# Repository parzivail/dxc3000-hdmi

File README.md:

# Sony DXC-3000A HDMI Conversion

This repository is split into multiple KiCad projects.

## MS9282 breakout

Contains the MS9282 breakout

Directory: `ms9282_carrier`

## DXC-3000A module template

Contains the blank PCB that matches the physical dimensions and 50-pin header of the backplane modules

Directory: `module_template`

## DXC-3000A module breakout

A few assets in this image:

The DXC-3000A backplane-to-FPC breakout board
* Directory: `module_breakout`

The video conditioner "shield" for the MS9282 breakout
* Directory: `ms9282_carrier_adapter`

Pairs with the MS9282 breakout from above.

## MS9282 module

Contains the complete MS9282-based EN-39 substitute for HDMI conversion. The image shows it in comparison with the original EN-39 module.

Directory: `ms9282_module`

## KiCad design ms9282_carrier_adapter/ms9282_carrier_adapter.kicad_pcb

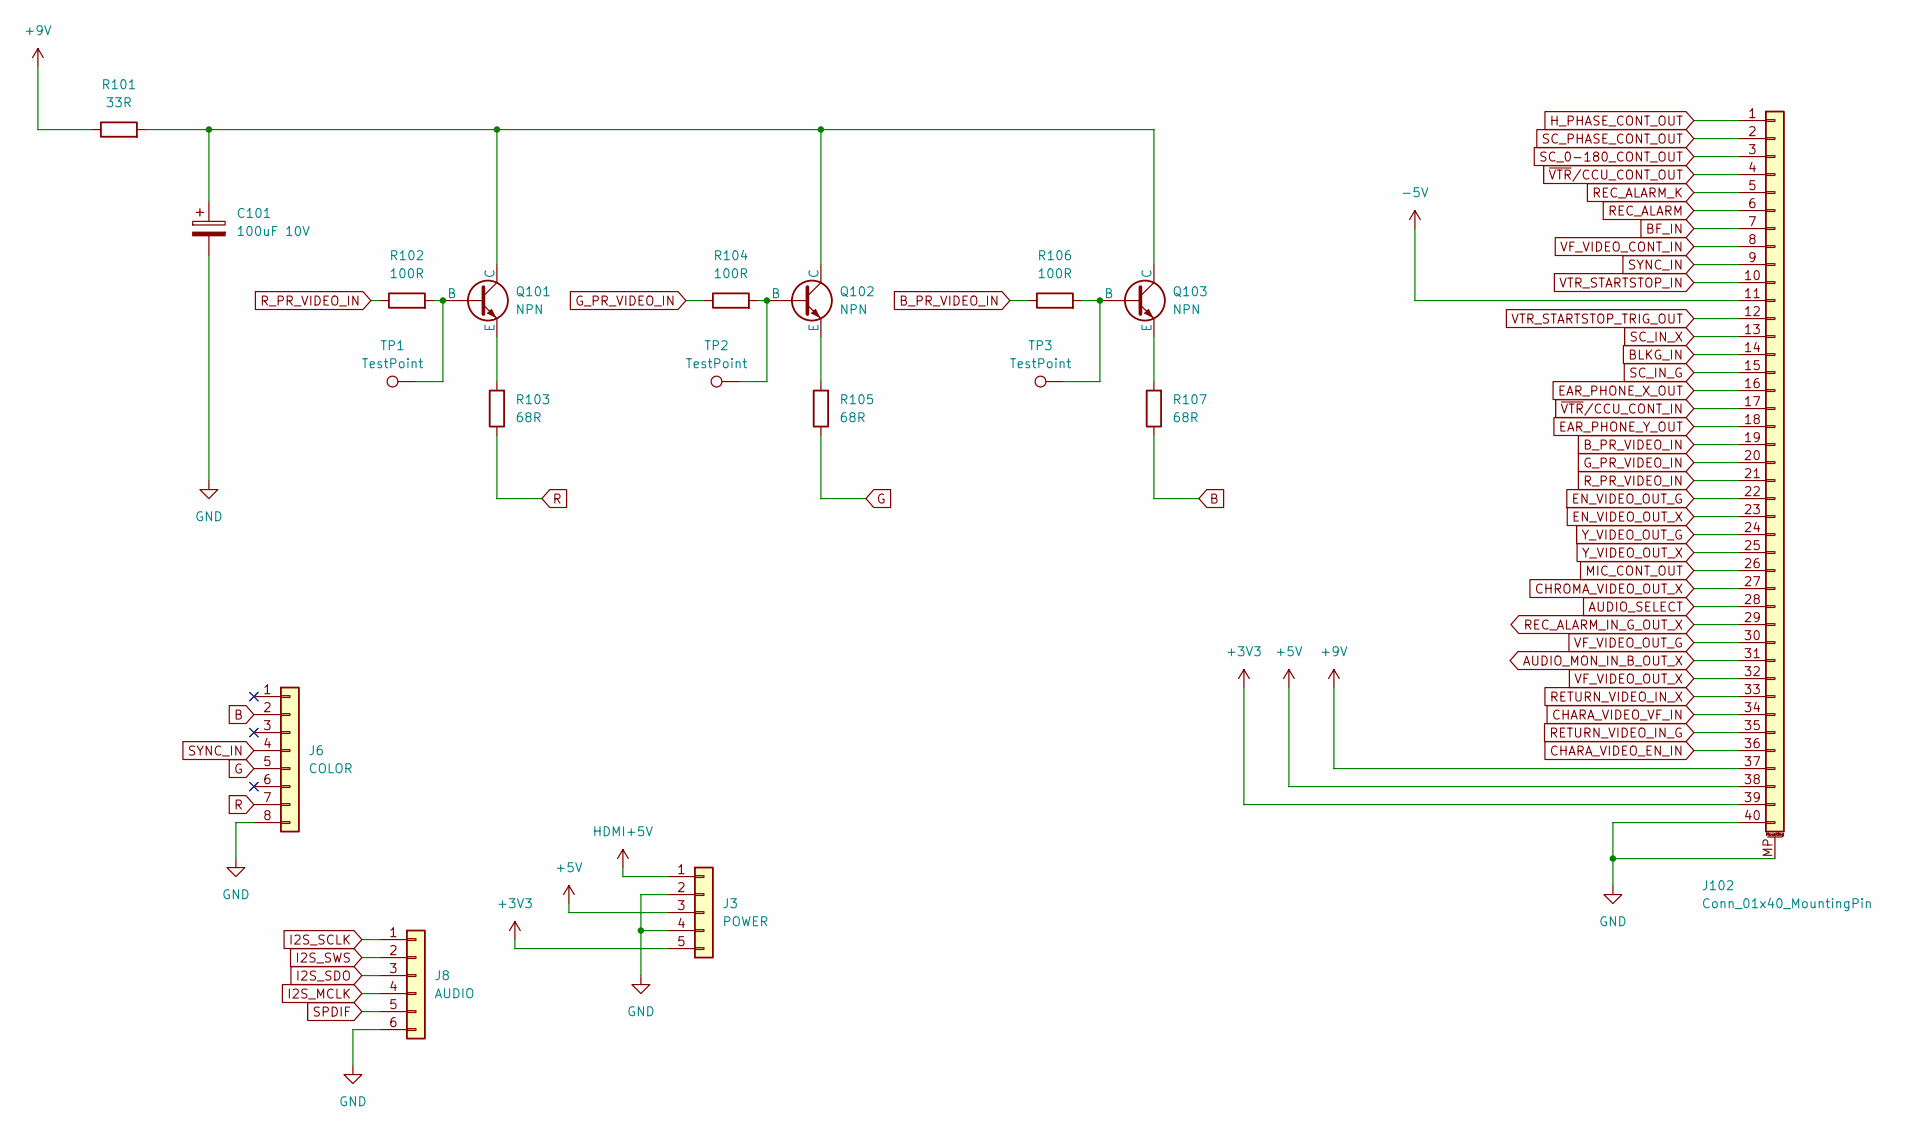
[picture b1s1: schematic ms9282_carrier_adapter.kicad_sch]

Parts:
C101: 100uF 10V; C_1206_3216Metric; LCSC Part C15008
J3: POWER; PinHeader_1x05_P2.54mm_Vertical
J6: COLOR; PinHeader_1x08_P2.54mm_Vertical
J8: AUDIO; PinHeader_1x06_P2.54mm_Vertical
J102: Conn_01x40_MountingPin; Hirose_FH12-40S-0.5SH_1x40-1MP_P0.50mm_Horizontal; LCSC Part C596725
Q101, Q102, Q103: NPN; SOT-23; LCSC Part C27829
R101: 33R; R_0402_1005Metric; LCSC Part C25105
R102, R104, R106: 100R; R_0402_1005Metric; LCSC Part C25076
R103, R105, R107: 68R; R_0603_1608Metric; LCSC Part C27592
TP1, TP2, TP3: TestPoint; TestPoint_Pad_D1.0mm

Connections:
+3V3: J3.5, J102.39
+5V: J3.3, J102.38
+9V: J102.37, R101.1
-5V: J102.11
AUDIO_MON_IN_B_OUT_X: J102.31
AUDIO_SELECT: J102.28
B: J6.2, R107.1
BF_IN: J102.7
BLKG_IN: J102.14
B_PR_VIDEO_IN: J102.19, R106.1
CHARA_VIDEO_EN_IN: J102.36
CHARA_VIDEO_VF_IN: J102.34
CHROMA_VIDEO_OUT_X: J102.27
EAR_PHONE_X_OUT: J102.16
EAR_PHONE_Y_OUT: J102.18
EN_VIDEO_OUT_G: J102.22
EN_VIDEO_OUT_X: J102.23
G: J6.5, R105.1
GND: C101.2, J3.2, J3.4, J6.8, J8.6, J102.40, J102.MP (MountPin)
G_PR_VIDEO_IN: J102.20, R104.1
HDMI+5V: J3.1
H_PHASE_CONT_OUT: J102.1
I2S_MCLK: J8.4
I2S_SCLK: J8.1
I2S_SDO: J8.3
I2S_SWS: J8.2
MIC_CONT_OUT: J102.26
unnamed: Q101.1 (B), R102.2, TP1.1
unnamed: C101.1, Q101.3 (C), Q102.3 (C), Q103.3 (C), R101.2
unnamed: Q101.2 (E), R103.2
unnamed: Q102.1 (B), R104.2, TP2.1
unnamed: Q102.2 (E), R105.2
unnamed: Q103.1 (B), R106.2, TP3.1
unnamed: Q103.2 (E), R107.2
R: J6.7, R103.1
REC_ALARM: J102.6
REC_ALARM_IN_G_OUT_X: J102.29
REC_ALARM_K: J102.5
RETURN_VIDEO_IN_G: J102.35
RETURN_VIDEO_IN_X: J102.33
R_PR_VIDEO_IN: J102.21, R102.1
SC_0-180_CONT_OUT: J102.3
SC_IN_G: J102.15
SC_IN_X: J102.13
SC_PHASE_CONT_OUT: J102.2
SPDIF: J8.5
SYNC_IN: J6.4, J102.9
VF_VIDEO_CONT_IN: J102.8
VF_VIDEO_OUT_G: J102.30
VF_VIDEO_OUT_X: J102.32
VTR_STARTSTOP_IN: J102.10
VTR_STARTSTOP_TRIG_OUT: J102.12
Y_VIDEO_OUT_G: J102.24
Y_VIDEO_OUT_X: J102.25
~VTR/CCU_CONT_IN: J102.17
~VTR/CCU_CONT_OUT: J102.4

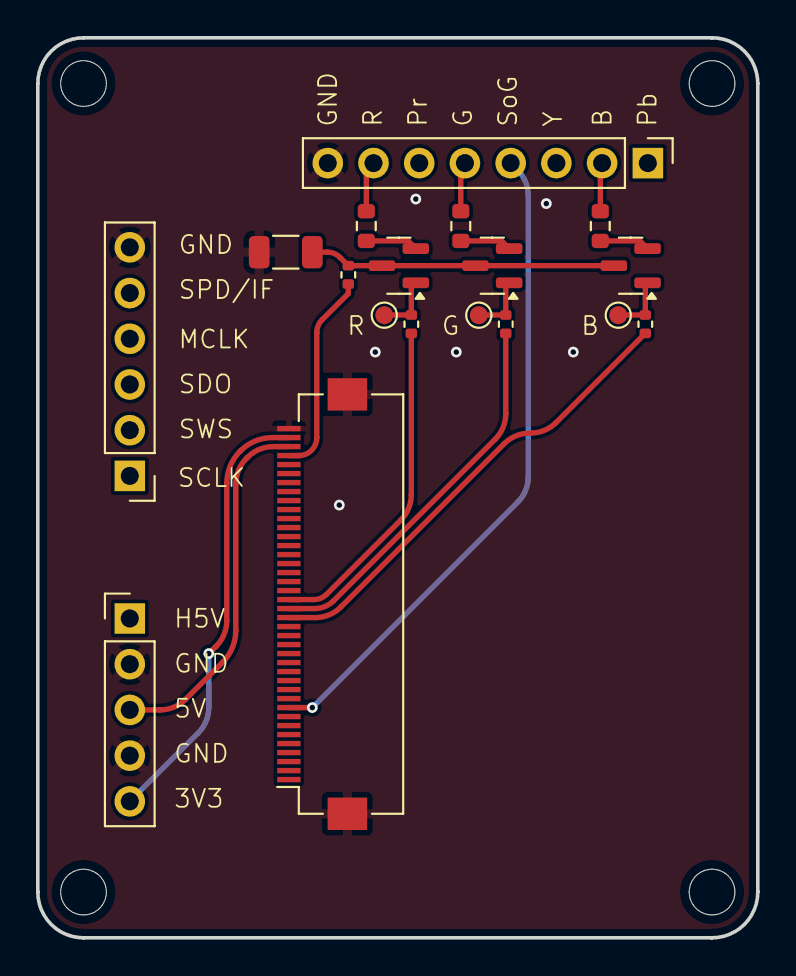
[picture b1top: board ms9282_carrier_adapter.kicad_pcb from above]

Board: 2 copper layers, 40.0 x 50.0 mm, 18 parts (0 on the bottom side), 18 nets.

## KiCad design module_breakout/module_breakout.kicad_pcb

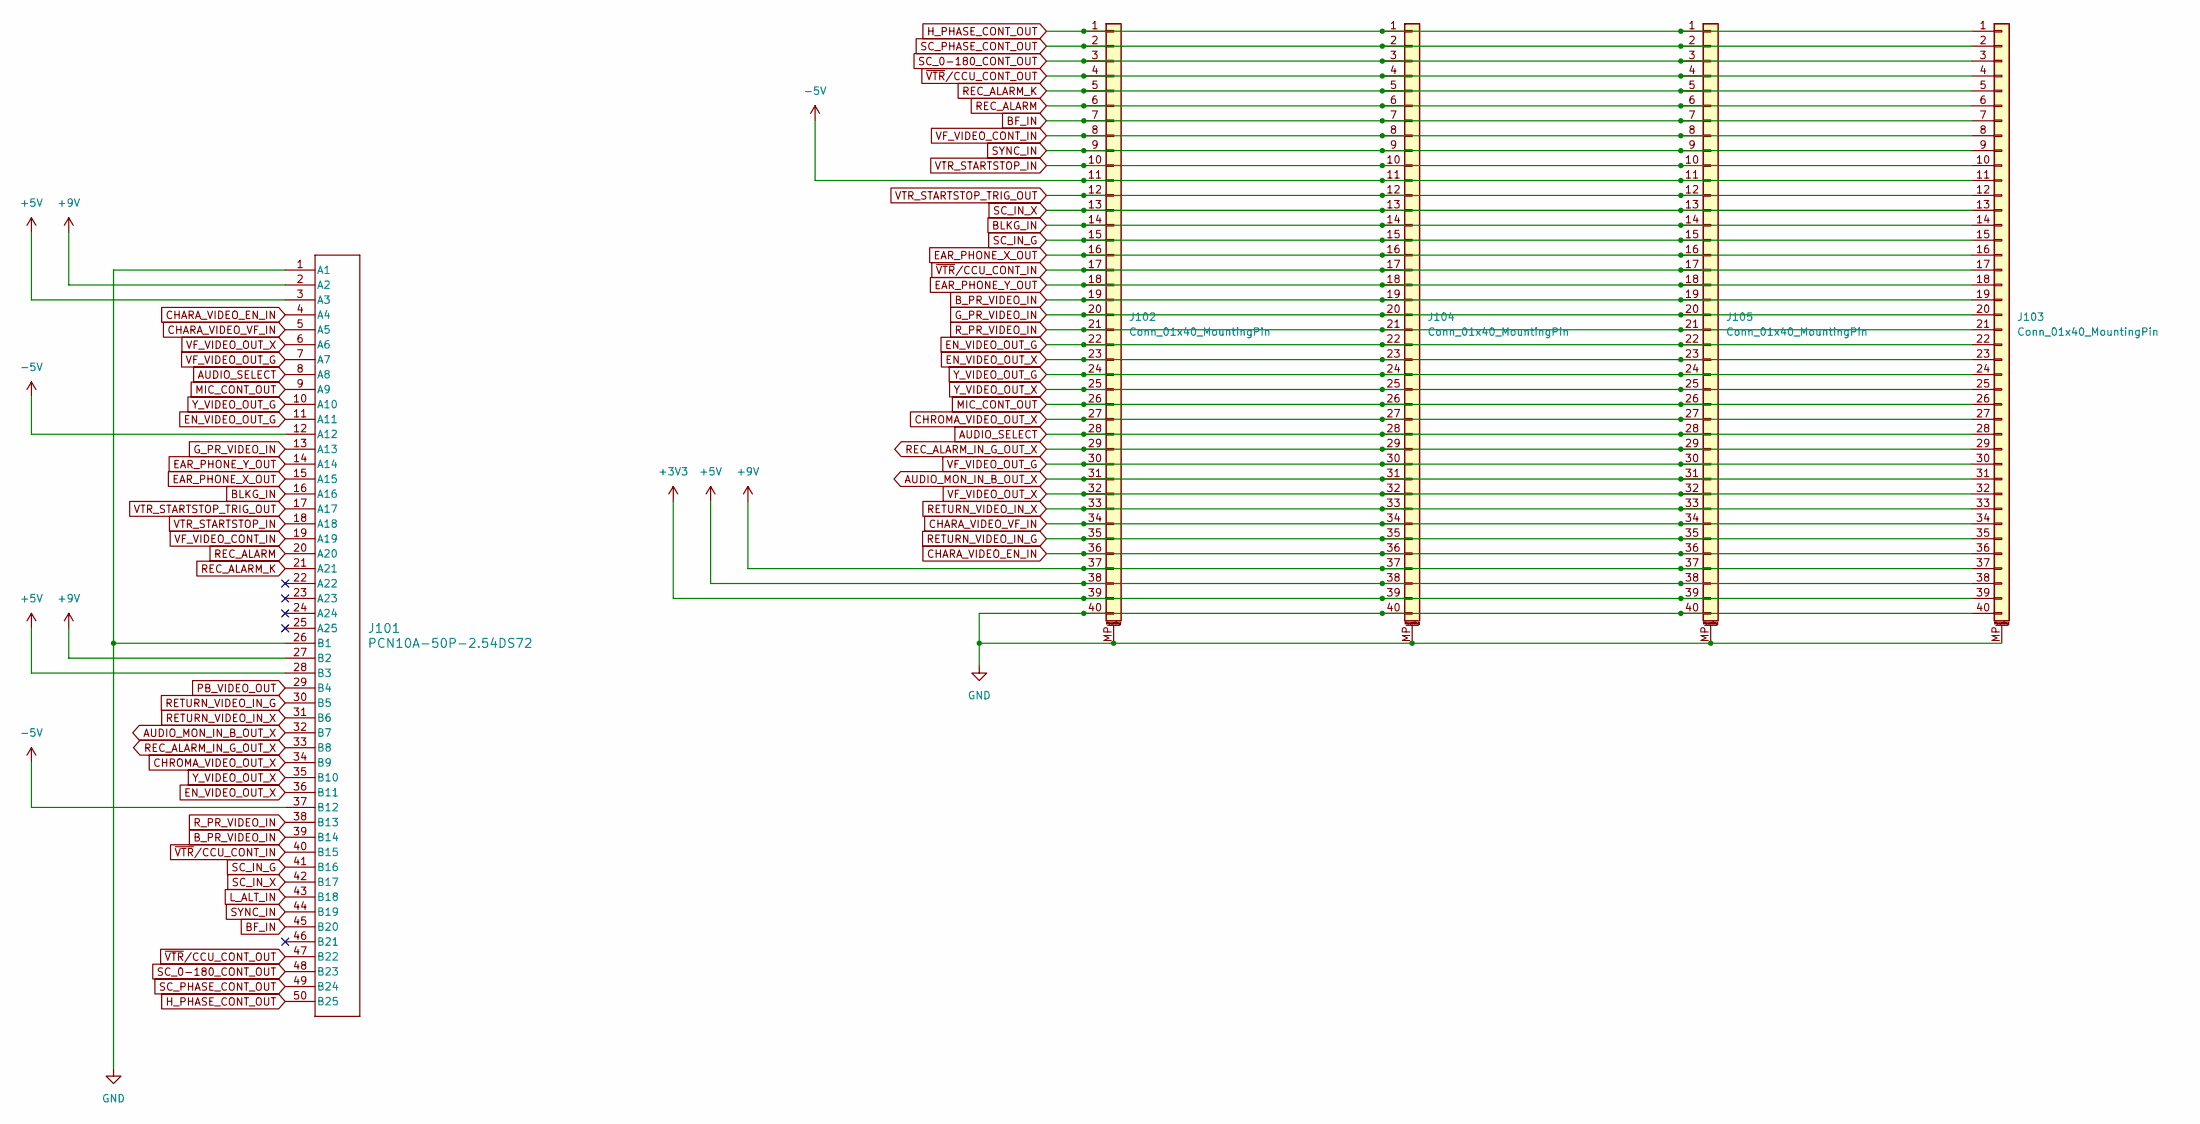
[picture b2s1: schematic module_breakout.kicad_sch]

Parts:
J101: PCN10A-50P-2.54DS72; CONN_PCN10A-50P_HIR
J102, J103, J104, J105: Conn_01x40_MountingPin; Hirose_FH12-40S-0.5SH_1x40-1MP_P0.50mm_Horizontal

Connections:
+3V3: J102.39, J103.39, J104.39, J105.39
+5V: J101.3 (A3), J101.28 (B3), J102.38, J103.38, J104.38, J105.38
+9V: J101.2 (A2), J101.27 (B2), J102.37, J103.37, J104.37, J105.37
-5V: J101.12 (A12), J101.37 (B12), J102.11, J103.11, J104.11, J105.11
AUDIO_MON_IN_B_OUT_X: J101.32 (B7), J102.31, J103.31, J104.31, J105.31
AUDIO_SELECT: J101.8 (A8), J102.28, J103.28, J104.28, J105.28
BF_IN: J101.45 (B20), J102.7, J103.7, J104.7, J105.7
BLKG_IN: J101.16 (A16), J102.14, J103.14, J104.14, J105.14
B_PR_VIDEO_IN: J101.39 (B14), J102.19, J103.19, J104.19, J105.19
CHARA_VIDEO_EN_IN: J101.4 (A4), J102.36, J103.36, J104.36, J105.36
CHARA_VIDEO_VF_IN: J101.5 (A5), J102.34, J103.34, J104.34, J105.34
CHROMA_VIDEO_OUT_X: J101.34 (B9), J102.27, J103.27, J104.27, J105.27
EAR_PHONE_X_OUT: J101.15 (A15), J102.16, J103.16, J104.16, J105.16
EAR_PHONE_Y_OUT: J101.14 (A14), J102.18, J103.18, J104.18, J105.18
EN_VIDEO_OUT_G: J101.11 (A11), J102.22, J103.22, J104.22, J105.22
EN_VIDEO_OUT_X: J101.36 (B11), J102.23, J103.23, J104.23, J105.23
GND: J101.1 (A1), J101.26 (B1), J102.40, J102.MP (MountPin), J103.40, J103.MP (MountPin), J104.40, J104.MP (MountPin), J105.40, J105.MP (MountPin)
G_PR_VIDEO_IN: J101.13 (A13), J102.20, J103.20, J104.20, J105.20
H_PHASE_CONT_OUT: J101.50 (B25), J102.1, J103.1, J104.1, J105.1
L_ALT_IN: J101.43 (B18)
MIC_CONT_OUT: J101.9 (A9), J102.26, J103.26, J104.26, J105.26
PB_VIDEO_OUT: J101.29 (B4)
REC_ALARM: J101.20 (A20), J102.6, J103.6, J104.6, J105.6
REC_ALARM_IN_G_OUT_X: J101.33 (B8), J102.29, J103.29, J104.29, J105.29
REC_ALARM_K: J101.21 (A21), J102.5, J103.5, J104.5, J105.5
RETURN_VIDEO_IN_G: J101.30 (B5), J102.35, J103.35, J104.35, J105.35
RETURN_VIDEO_IN_X: J101.31 (B6), J102.33, J103.33, J104.33, J105.33
R_PR_VIDEO_IN: J101.38 (B13), J102.21, J103.21, J104.21, J105.21
SC_0-180_CONT_OUT: J101.48 (B23), J102.3, J103.3, J104.3, J105.3
SC_IN_G: J101.41 (B16), J102.15, J103.15, J104.15, J105.15
SC_IN_X: J101.42 (B17), J102.13, J103.13, J104.13, J105.13
SC_PHASE_CONT_OUT: J101.49 (B24), J102.2, J103.2, J104.2, J105.2
SYNC_IN: J101.44 (B19), J102.9, J103.9, J104.9, J105.9
VF_VIDEO_CONT_IN: J101.19 (A19), J102.8, J103.8, J104.8, J105.8
VF_VIDEO_OUT_G: J101.7 (A7), J102.30, J103.30, J104.30, J105.30
VF_VIDEO_OUT_X: J101.6 (A6), J102.32, J103.32, J104.32, J105.32
VTR_STARTSTOP_IN: J101.18 (A18), J102.10, J103.10, J104.10, J105.10
VTR_STARTSTOP_TRIG_OUT: J101.17 (A17), J102.12, J103.12, J104.12, J105.12
Y_VIDEO_OUT_G: J101.10 (A10), J102.24, J103.24, J104.24, J105.24
Y_VIDEO_OUT_X: J101.35 (B10), J102.25, J103.25, J104.25, J105.25
~VTR/CCU_CONT_IN: J101.40 (B15), J102.17, J103.17, J104.17, J105.17
~VTR/CCU_CONT_OUT: J101.47 (B22), J102.4, J103.4, J104.4, J105.4

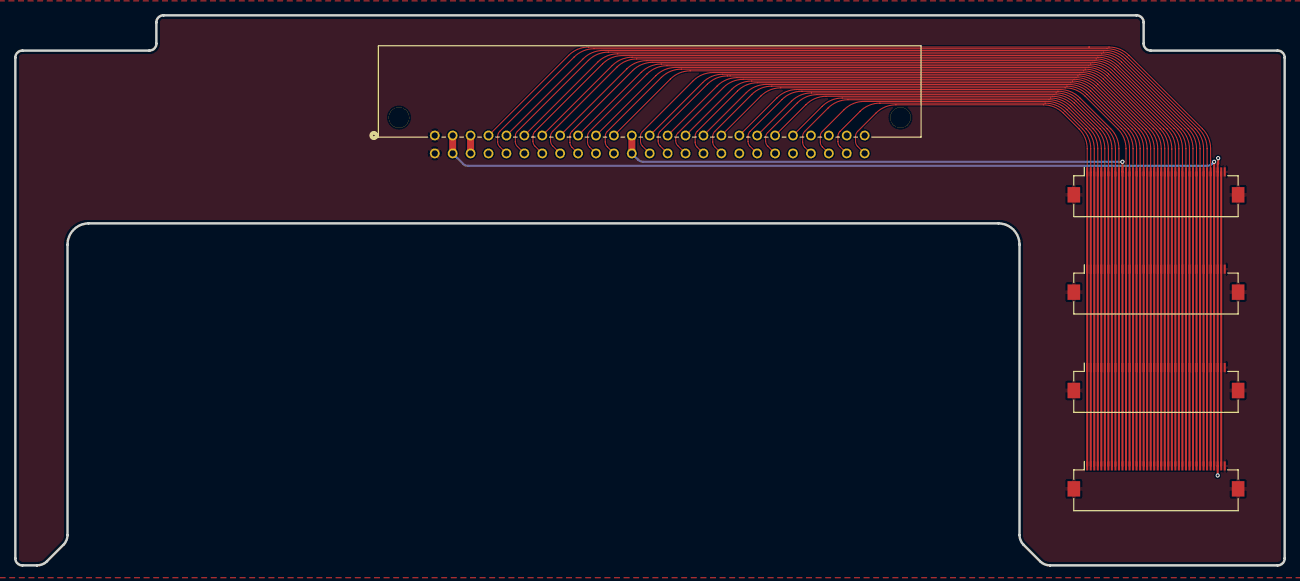
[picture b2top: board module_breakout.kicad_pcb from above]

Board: 2 copper layers, 180.0 x 78.0 mm, 5 parts (0 on the bottom side), 40 nets.

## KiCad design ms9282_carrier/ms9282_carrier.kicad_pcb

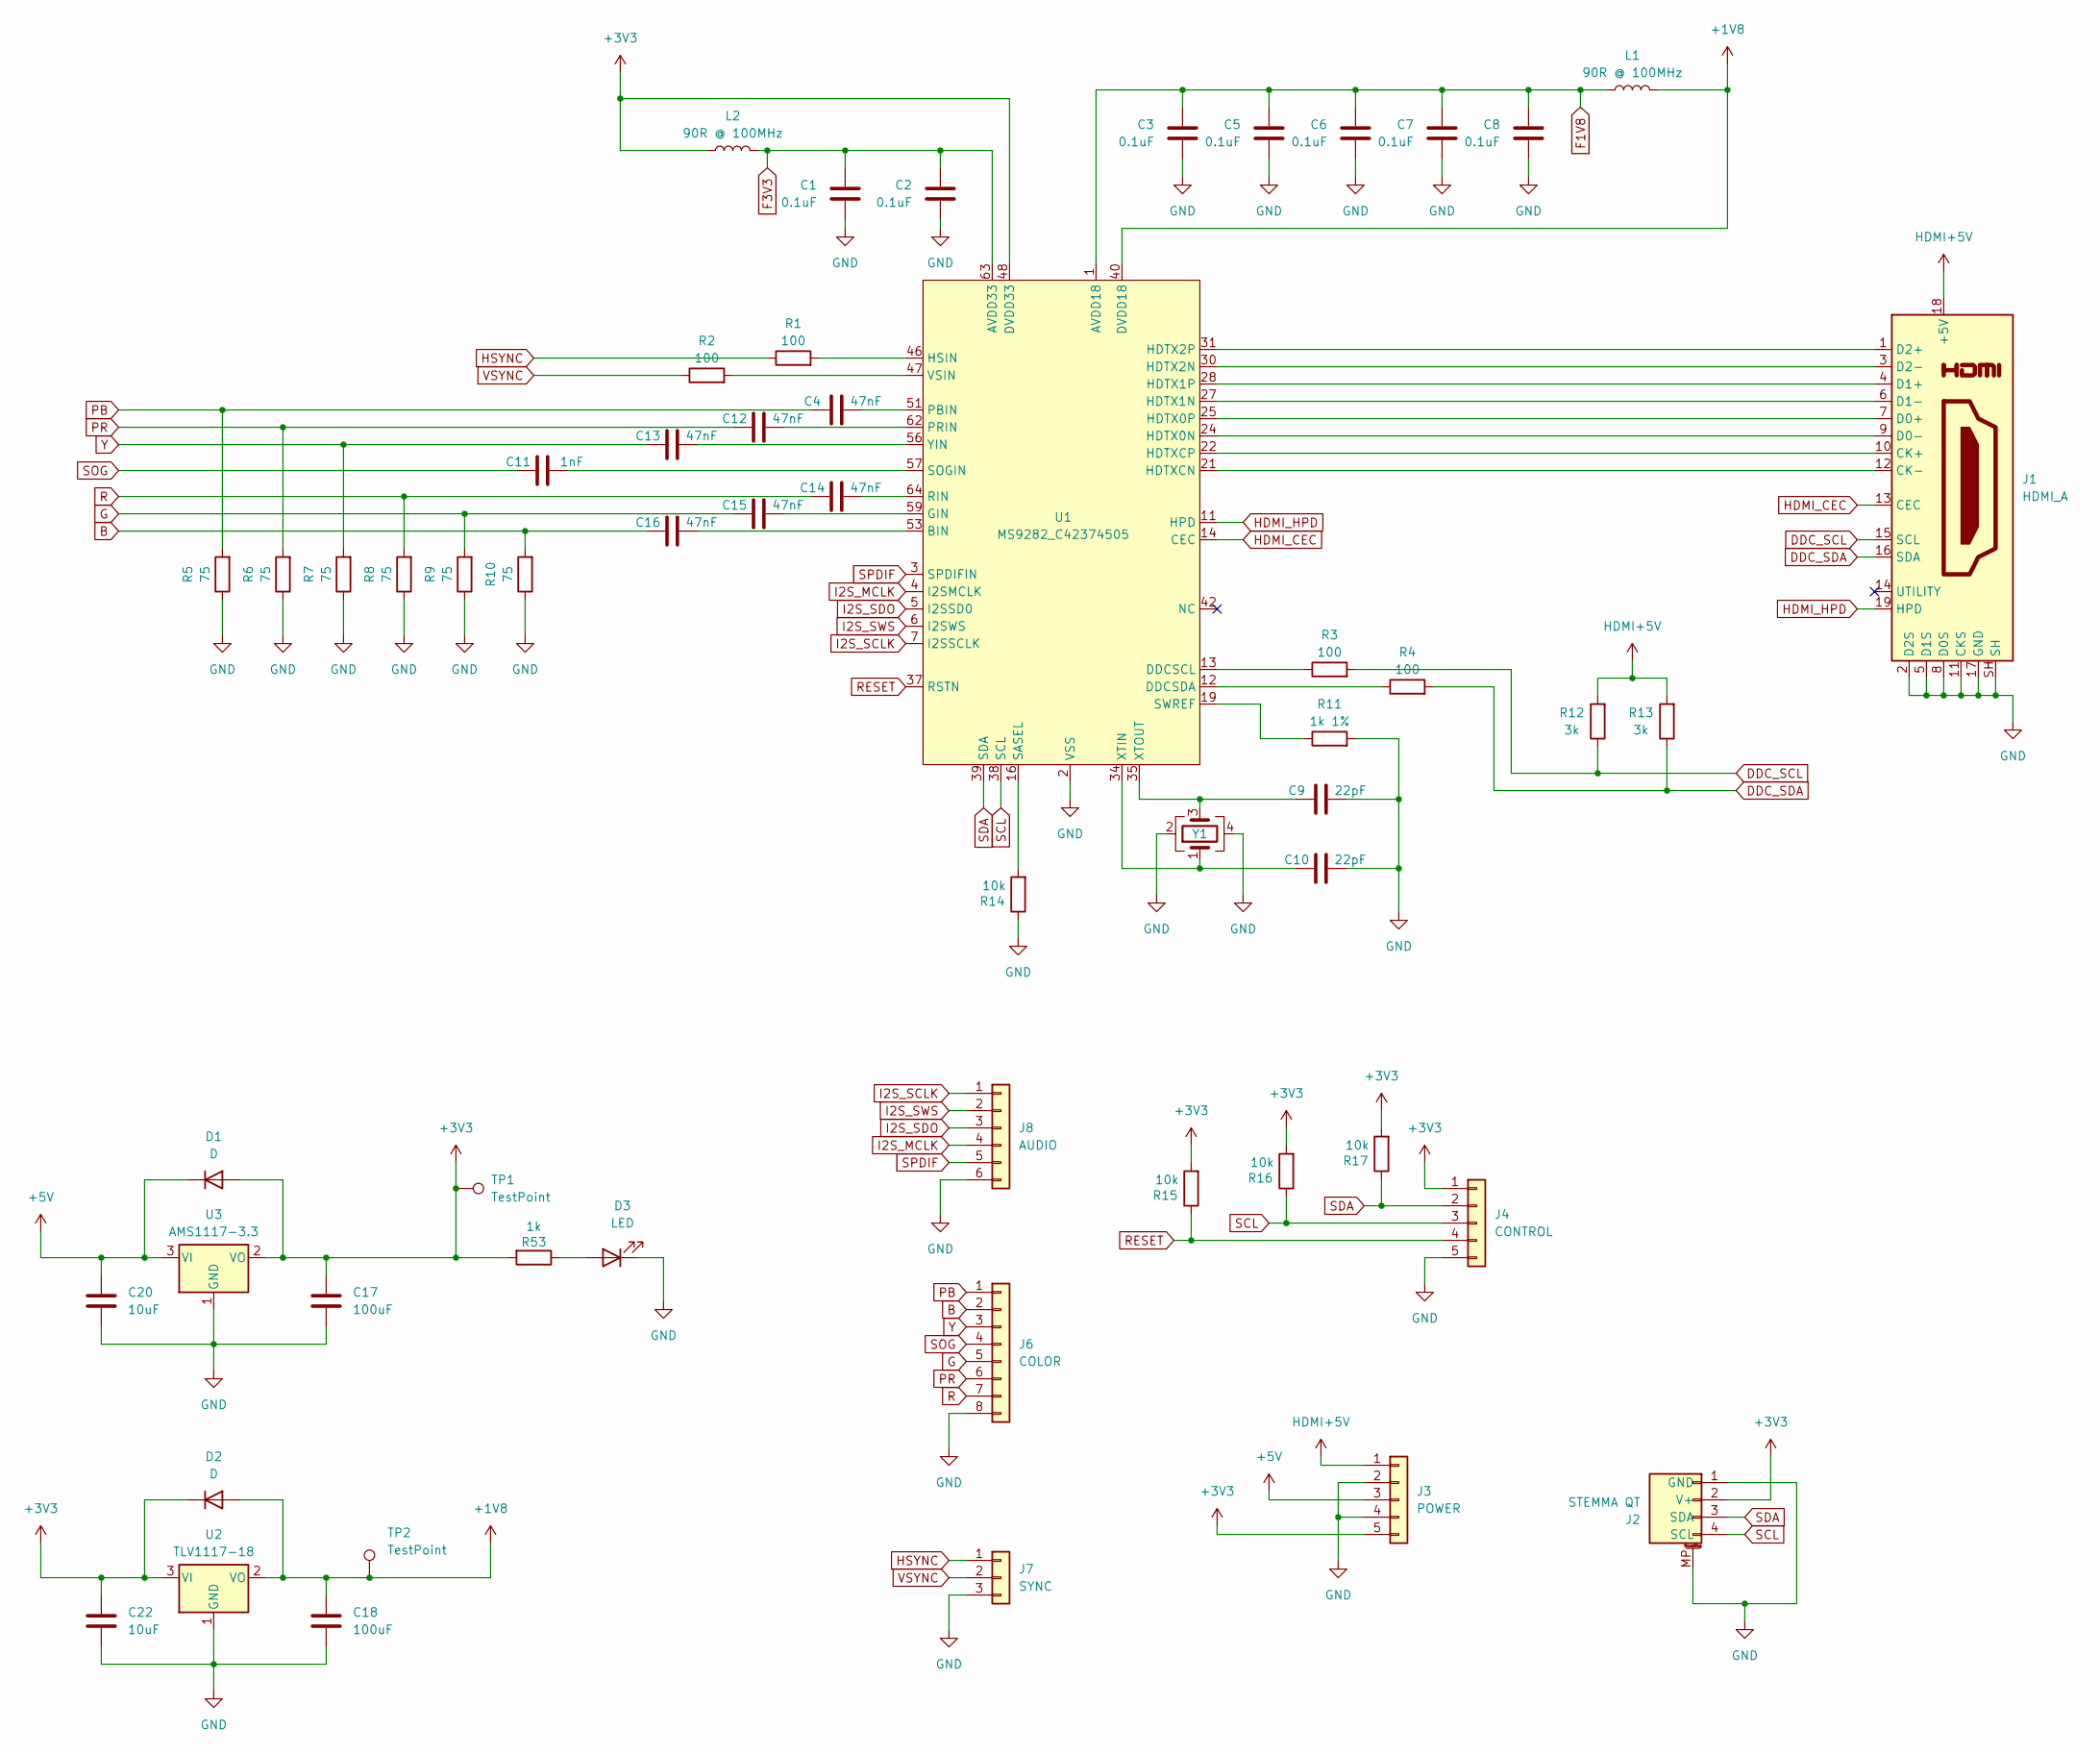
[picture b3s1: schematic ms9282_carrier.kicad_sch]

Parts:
C1, C2, C3, C5, C6, C7, C8: 0.1uF; C_0402_1005Metric; LCSC Part C1525
C4, C12, C13, C14, C15, C16: 47nF; C_0402_1005Metric; LCSC Part C307434
C9, C10: 22pF; C_0402_1005Metric; LCSC Part C1555
C11: 1nF; C_0402_1005Metric; LCSC Part C1523
C17, C18: 100uF; C_1206_3216Metric; LCSC Part C15008
C20, C22: 10uF; C_0402_1005Metric; LCSC Part C15525
D1, D2: D; D_SOD-123F; LCSC Part C64898
D3: LED; LED_0603_1608Metric; LCSC Part C2286
J1: HDMI_A; HDMI_A_Molex_208658-1001_Horizontal; LCSC Part C2858275
J2: STEMMA QT; JST_SH_SM04B-SRSS-TB_1x04-1MP_P1.00mm_Horizontal; LCSC Part C160404
J3: POWER; PinHeader_1x05_P2.54mm_Vertical
J4: CONTROL; PinHeader_1x05_P2.54mm_Vertical
J6: COLOR; PinHeader_1x08_P2.54mm_Vertical
J7: SYNC; PinHeader_1x03_P2.54mm_Vertical
J8: AUDIO; PinHeader_1x06_P2.54mm_Vertical
L1, L2: 90R @ 100MHz; L_0805_2012Metric; LCSC Part C1015
R1, R2, R3, R4: 100; R_0402_1005Metric; LCSC Part C25076
R5, R6, R7, R8, R9, R10: 75; R_0402_1005Metric; LCSC Part C25133
R11: 1k 1%; R_0402_1005Metric; LCSC Part C11702
R12, R13: 3k; R_0402_1005Metric; LCSC Part C25890
R14, R15, R16, R17: 10k; R_0402_1005Metric; LCSC Part C25744
R53: 1k; R_0402_1005Metric; LCSC Part C11702
TP1, TP2: TestPoint; TestPoint_Pad_D1.0mm
U1: MS9282_C42374505; LQFP-64_L10.0-W10.0-P0.50-LS12.0-BL; LCSC Part C42374505
U2: TLV1117-18; SOT-223-3_TabPin2; LCSC Part C2862410
U3: AMS1117-3.3; SOT-223-3_TabPin2; LCSC Part C6186
Y1: Crystal_GND24; Crystal_SMD_3225-4Pin_3.2x2.5mm; LCSC Part C654993

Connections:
+1V8: C18.1, D2.2 (A), L1.2, TP2.1, U1.9 (DVDD18), U1.40 (DVDD18), U2.2 (VO)
+3V3: C17.1, C22.1, D1.2 (A), D2.1 (K), J2.2 (V+), J3.5, J4.1, L2.1, R15.2, R16.2, R17.2, R53.2, TP1.1, U1.15 (DVDD33), U1.33 (DVDD33), U1.48 (DVDD33), U2.3 (VI), U3.2 (VO)
+5V: C20.1, D1.1 (K), J3.3, U3.3 (VI)
B: C16.2, J6.2, R10.2
DDC_SCL: J1.15 (SCL), R3.2, R12.1
DDC_SDA: J1.16 (SDA), R4.2, R13.1
F1V8: C3.1, C5.1, C6.1, C7.1, C8.1, L1.1, U1.1 (AVDD18), U1.23 (AVDD18), U1.29 (AVDD18), U1.55 (AVDD18), U1.61 (AVDD18)
F3V3: C1.1, C2.1, L2.2, U1.17 (AVDD33), U1.49 (AVDD33), U1.52 (AVDD33), U1.58 (AVDD33), U1.63 (AVDD33)
G: C15.2, J6.5, R9.2
GND: C1.2, C2.2, C3.2, C5.2, C6.2, C7.2, C8.2, C9.1, C10.1, C17.2, C18.2, C20.2, C22.2, D3.1 (K), J1.2 (D2S), J1.5 (D1S), J1.8 (D0S), J1.11 (CKS), J1.17 (GND), J1.SH, J2.1 (GND), J2.MP, J3.2, J3.4, J4.5, J6.8, J7.3, J8.6, R5.1, R6.1, R7.1, R8.1, R9.1, R10.1, R11.2, R14.1, U1.2 (VSS), U1.8 (VSS), U1.10 (VSS), U1.18 (VSS), U1.20 (VSS), U1.26 (VSS), U1.32 (VSS), U1.36 (VSS), U1.41 (VSS), U1.45 (VSS), U1.50 (VSS), U1.54 (VSS), U1.60 (VSS), U2.1 (GND), U3.1 (GND), Y1.2, Y1.4
HDMI+5V: J1.18 (+5V), J3.1, R12.2, R13.2
HDMI_CEC: J1.13 (CEC), U1.14 (CEC)
HDMI_HPD: J1.19 (HPD), U1.11 (HPD)
HSYNC: J7.1, R1.1
I2S_MCLK: J8.4, U1.4 (I2SMCLK)
I2S_SCLK: J8.1, U1.7 (I2SSCLK)
I2S_SDO: J8.3, U1.5 (I2SSD0)
I2S_SWS: J8.2, U1.6 (I2SWS)
unnamed: D3.2 (A), R53.1
unnamed: J1.10 (CK+), U1.22 (HDTXCP)
unnamed: J1.12 (CK-), U1.21 (HDTXCN)
unnamed: J1.7 (D0+), U1.25 (HDTX0P)
unnamed: J1.9 (D0-), U1.24 (HDTX0N)
unnamed: J1.4 (D1+), U1.28 (HDTX1P)
unnamed: J1.6 (D1-), U1.27 (HDTX1N)
unnamed: J1.1 (D2+), U1.31 (HDTX2P)
unnamed: J1.3 (D2-), U1.30 (HDTX2N)
unnamed: C16.1, U1.53 (BIN)
unnamed: R3.1, U1.13 (DDCSCL)
unnamed: R4.1, U1.12 (DDCSDA)
unnamed: C15.1, U1.59 (GIN)
unnamed: R1.2, U1.46 (HSIN)
unnamed: C4.1, U1.51 (PBIN)
unnamed: C12.1, U1.62 (PRIN)
unnamed: C14.1, U1.64 (RIN)
unnamed: R14.2, U1.16 (SASEL)
unnamed: C11.1, U1.57 (SOGIN)
unnamed: R11.1, U1.19 (SWREF)
unnamed: R2.2, U1.47 (VSIN)
unnamed: C10.2, U1.34 (XTIN), Y1.1
unnamed: C9.2, U1.35 (XTOUT), Y1.3
unnamed: C13.1, U1.56 (YIN)
PB: C4.2, J6.1, R5.2
PR: C12.2, J6.6, R6.2
R: C14.2, J6.7, R8.2
RESET: J4.4, R15.1, U1.37 (RSTN)
SCL: J2.4 (SCL), J4.3, R16.1, U1.38 (SCL)
SDA: J2.3 (SDA), J4.2, R17.1, U1.39 (SDA)
SOG: C11.2, J6.4
SPDIF: J8.5, U1.3 (SPDIFIN)
VSYNC: J7.2, R2.1
Y: C13.2, J6.3, R7.2

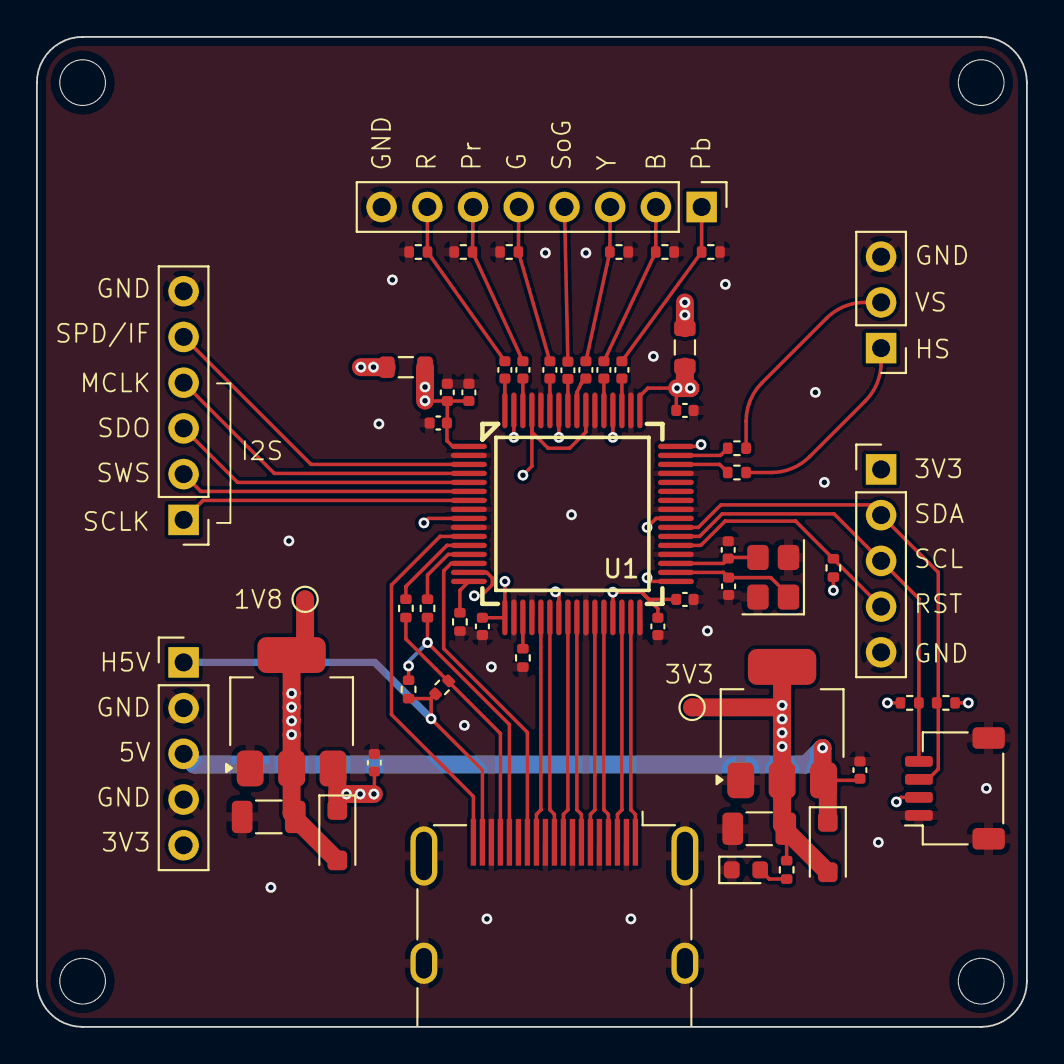
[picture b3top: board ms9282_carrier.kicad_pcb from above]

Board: 4 copper layers, 55.0 x 55.0 mm, 56 parts (0 on the bottom side), 52 nets.
